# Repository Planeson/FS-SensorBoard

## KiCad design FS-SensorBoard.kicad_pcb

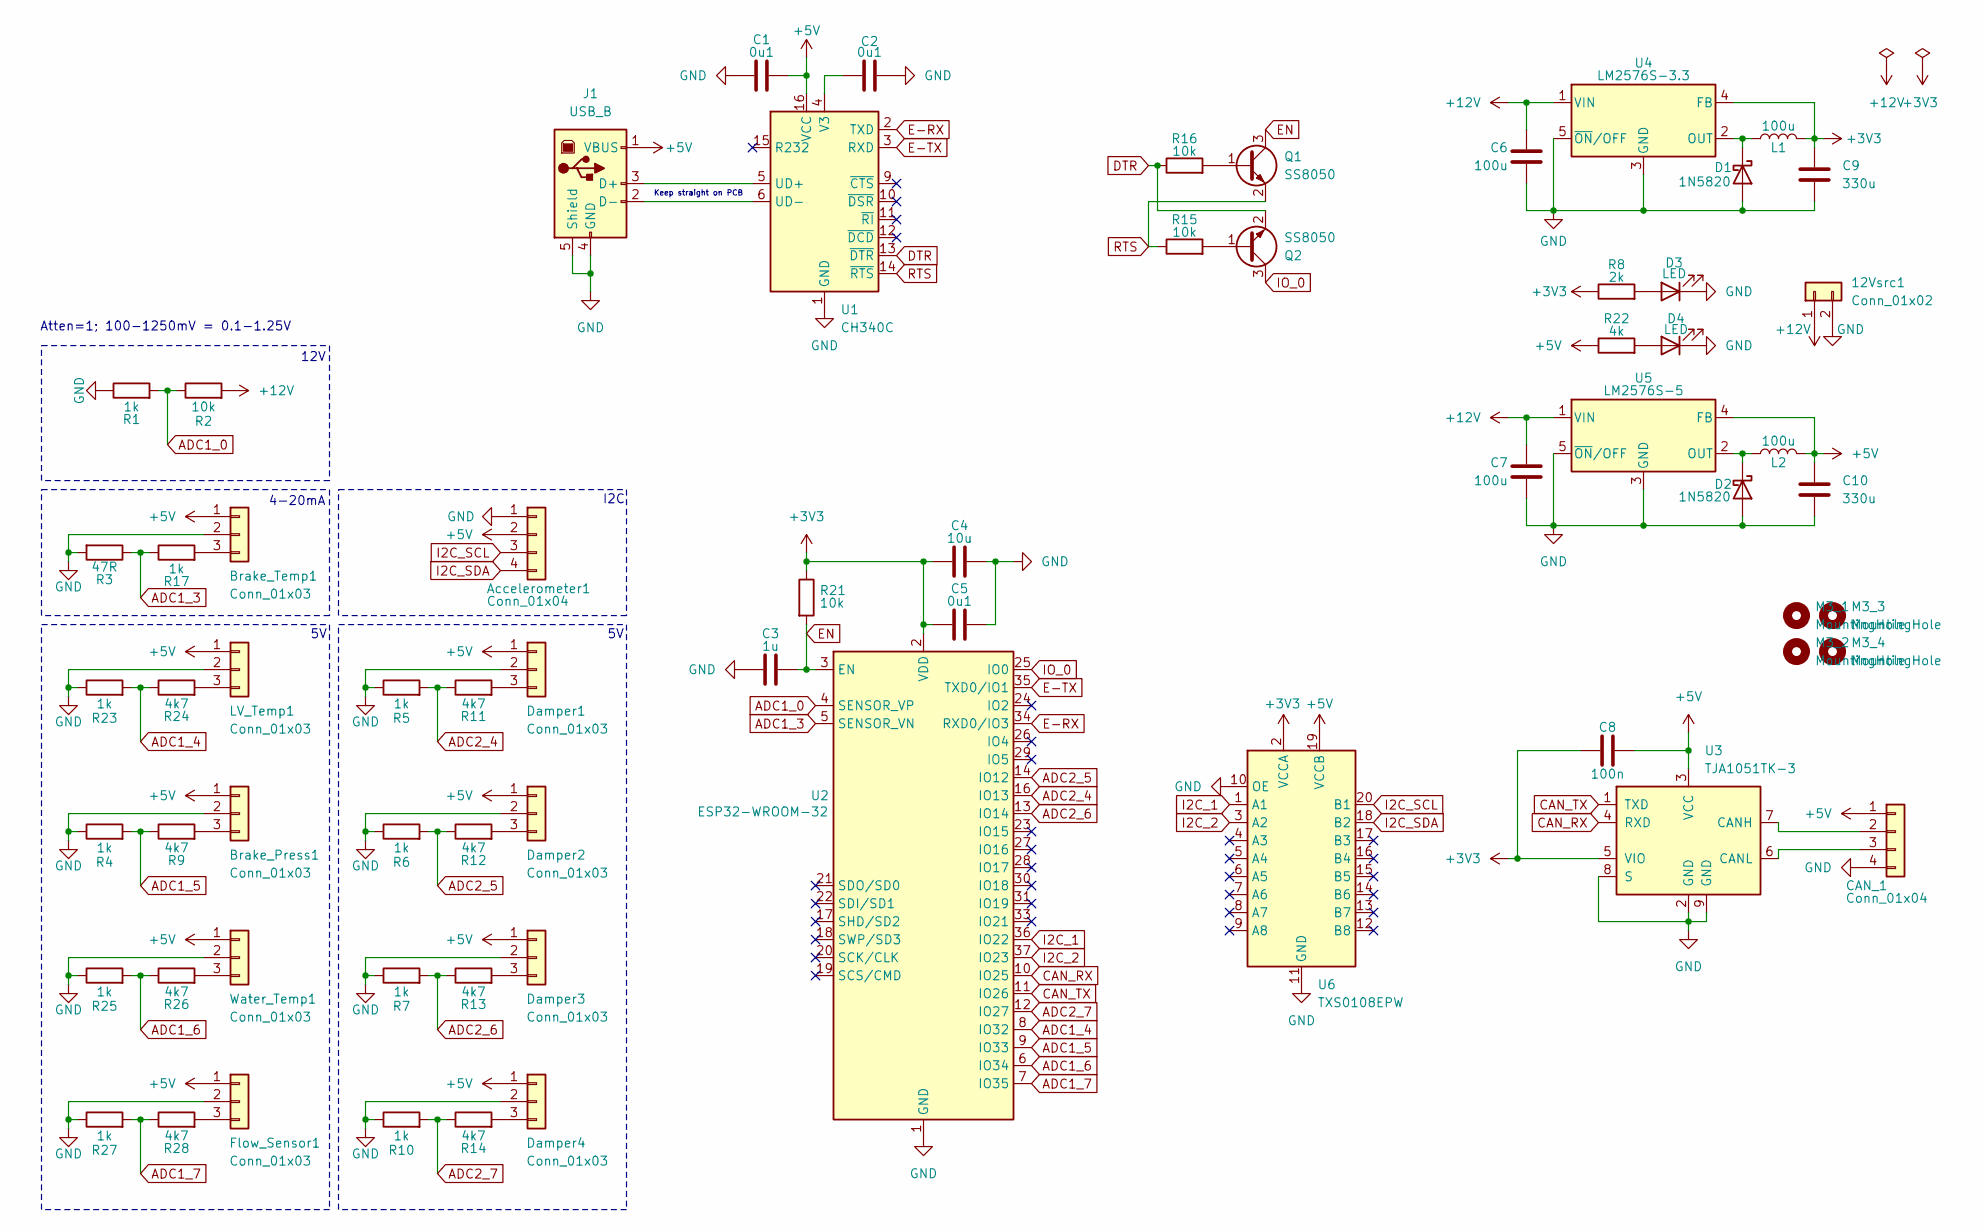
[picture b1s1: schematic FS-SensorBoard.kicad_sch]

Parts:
12Vsrc1: Conn_01x02; JST_VH_B2P-VH_1x02_P3.96mm_Vertical
Accelerometer1: Conn_01x04; JST_XH_B4B-XH-A_1x04_P2.50mm_Vertical
Brake_Press1: Conn_01x03; JST_XH_B3B-XH-A_1x03_P2.50mm_Vertical
Brake_Temp1: Conn_01x03; JST_XH_B3B-XH-A_1x03_P2.50mm_Vertical
C1, C2, C5: 0u1; C_1206_3216Metric_Pad1.33x1.80mm_HandSolder
C3: 1u; C_1206_3216Metric_Pad1.33x1.80mm_HandSolder
C4: 10u; C_1206_3216Metric_Pad1.33x1.80mm_HandSolder
C6, C7: 100u; C_1206_3216Metric_Pad1.33x1.80mm_HandSolder
C8: 100n; C_1206_3216Metric_Pad1.33x1.80mm_HandSolder
C9, C10: 330u; C_1808_4520Metric_Pad1.72x2.30mm_HandSolder
CAN_1: Conn_01x04; JST_XH_B4B-XH-A_1x04_P2.50mm_Vertical
D1, D2: 1N5820; D_DO-201AD_P15.24mm_Horizontal
D3, D4: LED; LED_1206_3216Metric_Pad1.42x1.75mm_HandSolder
Damper1, Damper2, Damper3, Damper4: Conn_01x03; JST_XH_B3B-XH-A_1x03_P2.50mm_Vertical
Flow_Sensor1: Conn_01x03; JST_XH_B3B-XH-A_1x03_P2.50mm_Vertical
J1: USB_B; USB_B_TE_5787834_Vertical
L1, L2: 100u; L_Bourns-SRN4018
LV_Temp1: Conn_01x03; JST_XH_B3B-XH-A_1x03_P2.50mm_Vertical
M3_1, M3_2, M3_3, M3_4: MountingHole; MountingHole_3.2mm_M3
Q1, Q2: SS8050; SOT-23
R1, R4, R5, R6, R7, R10, R17, R23, R25, R27: 1k; R_1206_3216Metric_Pad1.30x1.75mm_HandSolder
R2, R15, R16, R21: 10k; R_1206_3216Metric_Pad1.30x1.75mm_HandSolder
R3: 47R; R_1206_3216Metric_Pad1.30x1.75mm_HandSolder
R8: 2k; R_1206_3216Metric_Pad1.30x1.75mm_HandSolder
R9, R11, R12, R13, R14, R24, R26, R28: 4k7; R_1206_3216Metric_Pad1.30x1.75mm_HandSolder
R22: 4k; R_1206_3216Metric_Pad1.30x1.75mm_HandSolder
U1: CH340C; SOIC-16_3.9x9.9mm_P1.27mm
U2: ESP32-WROOM-32; ESP32-WROOM-32-LongPad
U3: TJA1051TK-3; DFN-8-1EP_3x3mm_P0.65mm_EP1.55x2.4mm
U4: LM2576S-3.3; TO-263-5_TabPin3
U5: LM2576S-5; TO-263-5_TabPin3
U6: TXS0108EPW; TSSOP-20_4.4x6.5mm_P0.65mm
Water_Temp1: Conn_01x03; JST_XH_B3B-XH-A_1x03_P2.50mm_Vertical

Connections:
+3V3: C4.1, C5.1, C8.1, C9.1, L1.2, R8.1, R21.1, U2.2 (VDD), U3.5 (VIO), U4.4 (FB), U6.2 (VCCA)
+5V: Accelerometer1.2, Brake_Press1.1, Brake_Temp1.1, C1.2, C8.2, C10.1, CAN_1.1, Damper1.1, Damper2.1, Damper3.1, Damper4.1, Flow_Sensor1.1, J1.1 (VBUS), L2.2, LV_Temp1.1, R22.1, U1.16 (VCC), U3.3 (VCC), U5.4 (FB), U6.19 (VCCB), Water_Temp1.1
+12V: 12Vsrc1.1, C6.1, C7.1, R2.2, U4.1 (VIN), U5.1 (VIN)
ADC1_0: R1.2, R2.1, U2.4 (SENSOR_VP)
ADC1_3: R3.1, R17.1, U2.5 (SENSOR_VN)
ADC1_4: R23.2, R24.1, U2.8 (IO32)
ADC1_5: R4.2, R9.1, U2.9 (IO33)
ADC1_6: R25.2, R26.1, U2.6 (IO34)
ADC1_7: R27.2, R28.1, U2.7 (IO35)
ADC2_4: R5.2, R11.1, U2.16 (IO13)
ADC2_5: R6.2, R12.1, U2.14 (IO12)
ADC2_6: R7.2, R13.1, U2.13 (IO14)
ADC2_7: R10.2, R14.1, U2.12 (IO27)
CAN_RX: U2.10 (IO25), U3.4 (RXD)
CAN_TX: U2.11 (IO26), U3.1 (TXD)
DTR: Q2.2 (E), R16.1, U1.13 (~DTR)
E-RX: U1.2 (TXD), U2.34 (RXD0/IO3)
E-TX: U1.3 (RXD), U2.35 (TXD0/IO1)
EN: C3.2, Q1.3 (C), R21.2, U2.3 (EN)
GND: 12Vsrc1.2, Accelerometer1.1, Brake_Press1.2, Brake_Temp1.2, C1.1, C2.1, C3.1, C4.2, C5.2, C6.2, C7.2, C9.2, C10.2, CAN_1.4, D1.2 (A), D2.2 (A), D3.1 (K), D4.1 (K), Damper1.2, Damper2.2, Damper3.2, Damper4.2, Flow_Sensor1.2, J1.4 (GND), J1.5 (Shield), LV_Temp1.2, R1.1, R3.2, R4.1, R5.1, R6.1, R7.1, R10.1, R23.1, R25.1, R27.1, U1.1 (GND), U2.1 (GND), U2.15 (GND), U2.38 (GND), U2.39 (GND), U3.2 (GND), U3.8 (S), U3.9 (GND), U4.3 (GND), U4.5 (~ON/OFF), U5.3 (GND), U5.5 (~ON/OFF), U6.10 (OE), U6.11 (GND), Water_Temp1.2
I2C_1: U2.36 (IO22), U6.1 (A1)
I2C_2: U2.37 (IO23), U6.3 (A2)
I2C_SCL: Accelerometer1.3, U6.20 (B1)
I2C_SDA: Accelerometer1.4, U6.18 (B2)
IO_0: Q2.3 (C), U2.25 (IO0)
unnamed: Brake_Press1.3, R9.2
unnamed: Brake_Temp1.3, R17.2
unnamed: CAN_1.2, U3.7 (CANH)
unnamed: CAN_1.3, U3.6 (CANL)
unnamed: D1.1 (K), L1.1, U4.2 (OUT)
unnamed: D2.1 (K), L2.1, U5.2 (OUT)
unnamed: D3.2 (A), R8.2
unnamed: D4.2 (A), R22.2
unnamed: Damper1.3, R11.2
unnamed: Damper2.3, R12.2
unnamed: Damper3.3, R13.2
unnamed: Damper4.3, R14.2
unnamed: Flow_Sensor1.3, R28.2
unnamed: J1.3 (D+), U1.5 (UD+)
unnamed: J1.2 (D-), U1.6 (UD-)
unnamed: LV_Temp1.3, R24.2
unnamed: Q1.1 (B), R16.2
unnamed: Q2.1 (B), R15.2
unnamed: C2.2, U1.4 (V3)
unnamed: R26.2, Water_Temp1.3
RTS: Q1.2 (E), R15.1, U1.14 (~RTS)

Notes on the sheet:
4-20mA
Keep straight on PCB
12V
Atten=1; 100-1250mV = 0.1-1.25V
I2C

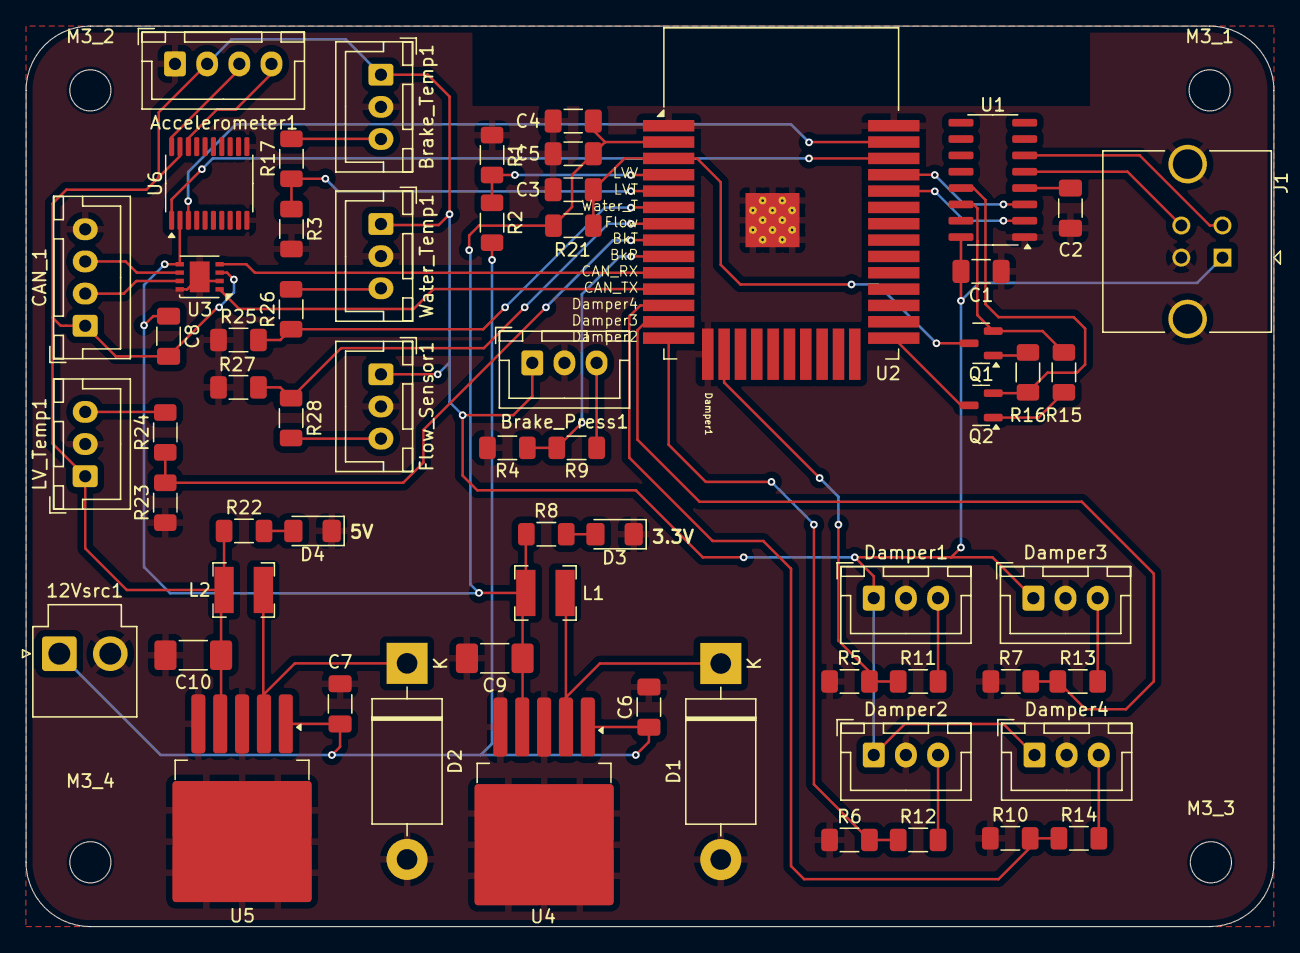
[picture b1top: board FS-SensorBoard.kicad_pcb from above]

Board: 2 copper layers, 97.0 x 70.0 mm, 66 parts (0 on the bottom side), 46 nets.

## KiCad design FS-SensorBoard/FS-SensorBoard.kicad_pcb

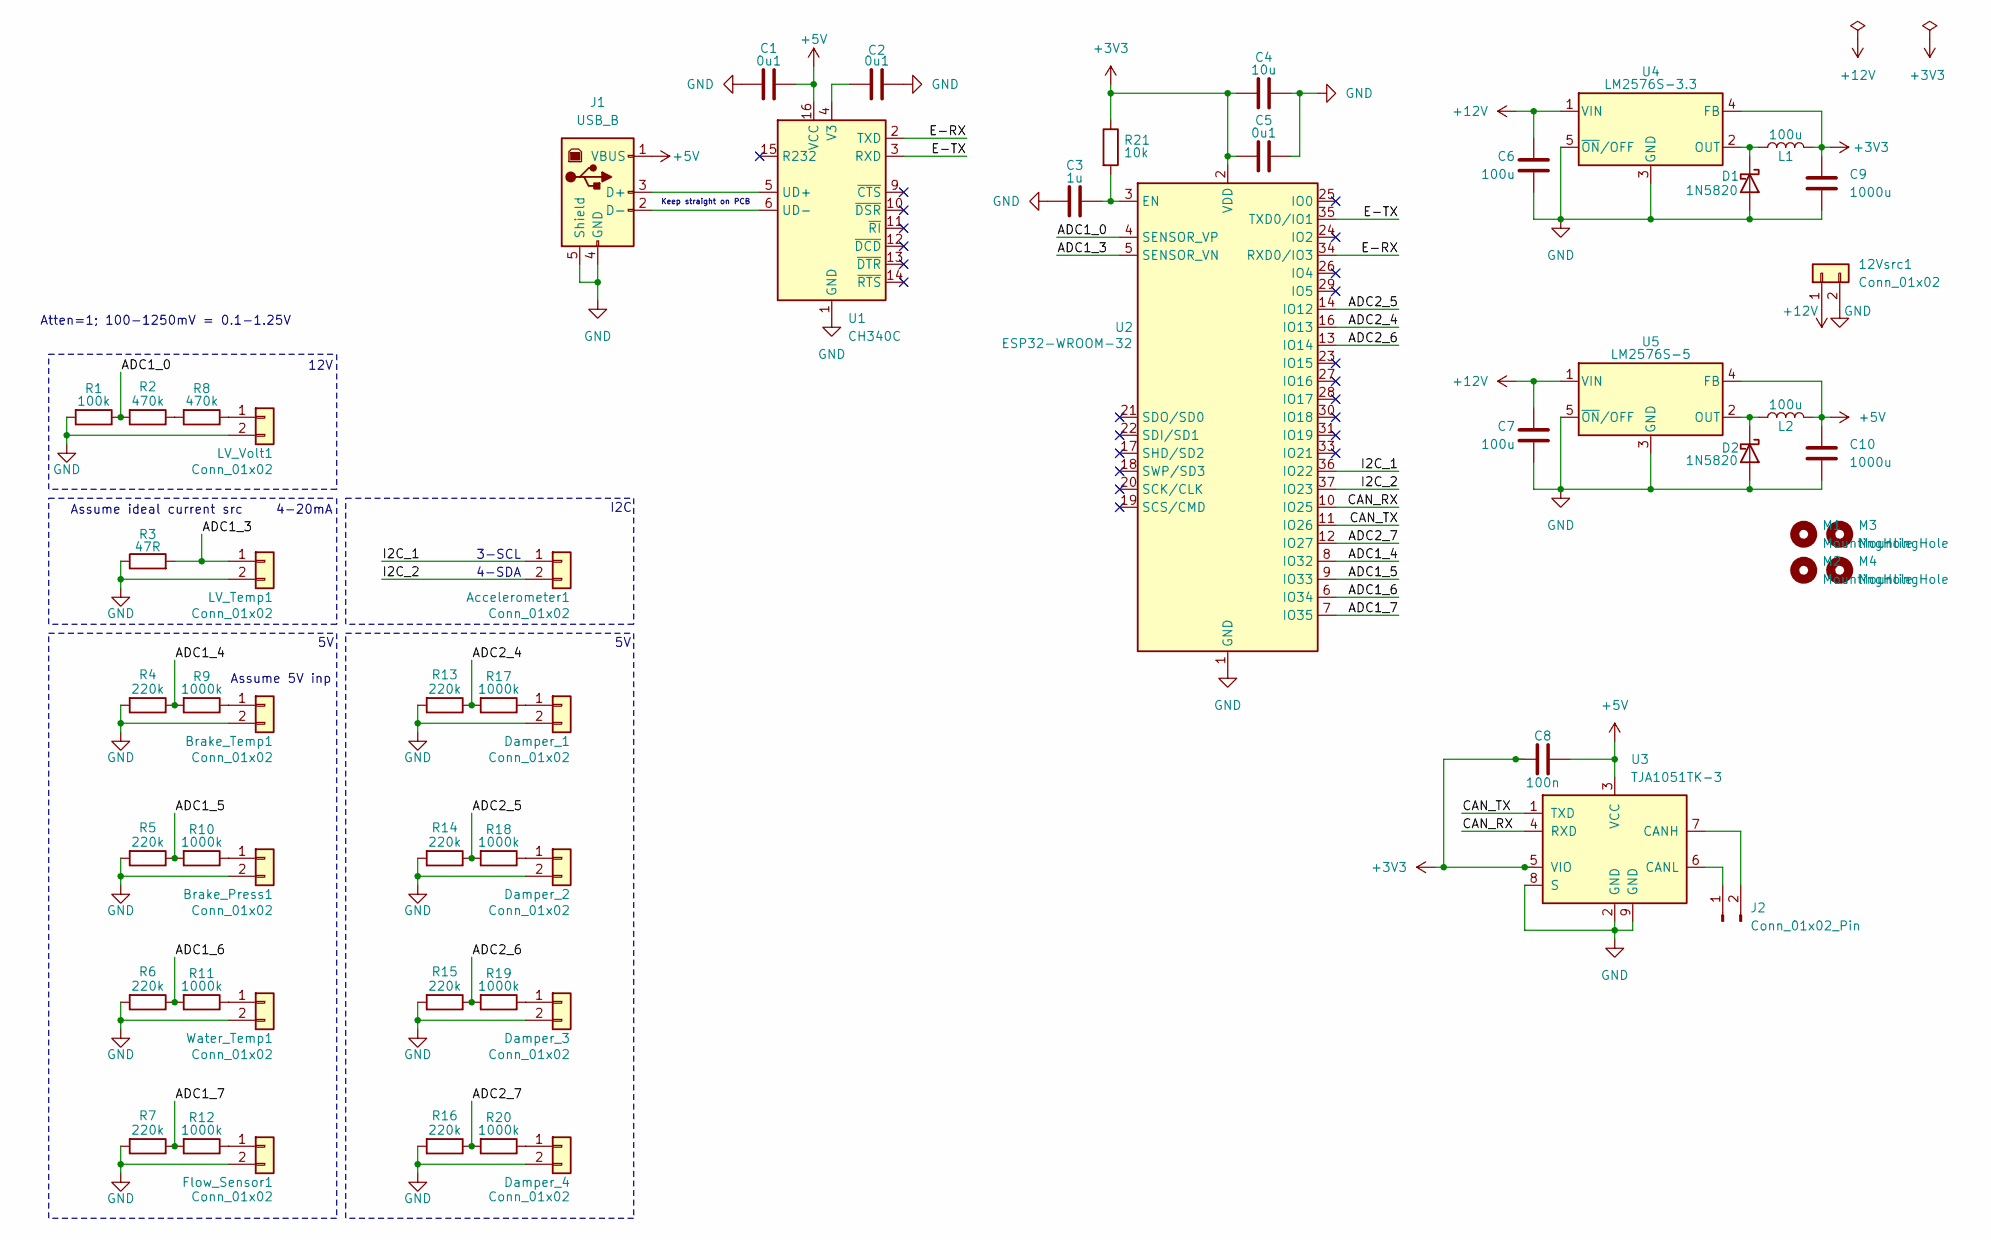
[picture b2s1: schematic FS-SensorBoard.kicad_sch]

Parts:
12Vsrc1: Conn_01x02; JST_VH_B2P-VH_1x02_P3.96mm_Vertical
Accelerometer1: Conn_01x02; JST_XH_B2B-XH-A_1x02_P2.50mm_Vertical
Brake_Press1: Conn_01x02; JST_XH_B2B-XH-A_1x02_P2.50mm_Vertical
Brake_Temp1: Conn_01x02; JST_XH_B2B-XH-A_1x02_P2.50mm_Vertical
C1, C2, C5: 0u1; C_1206_3216Metric_Pad1.33x1.80mm_HandSolder
C3: 1u; C_1206_3216Metric_Pad1.33x1.80mm_HandSolder
C4: 10u; C_1206_3216Metric_Pad1.33x1.80mm_HandSolder
C6, C7: 100u; C_1206_3216Metric_Pad1.33x1.80mm_HandSolder
C8: 100n; C_1206_3216Metric_Pad1.33x1.80mm_HandSolder
C9, C10: 1000u; C_1206_3216Metric_Pad1.33x1.80mm_HandSolder
D1, D2: 1N5820; D_DO-201AD_P15.24mm_Horizontal
Damper_1, Damper_2, Damper_3, Damper_4: Conn_01x02; JST_XH_B2B-XH-A_1x02_P2.50mm_Vertical
Flow_Sensor1: Conn_01x02; JST_XH_B2B-XH-A_1x02_P2.50mm_Vertical
J1: USB_B; USB_B_TE_5787834_Vertical
J2: Conn_01x02_Pin; JST_XH_B2B-XH-A_1x02_P2.50mm_Vertical
L1, L2: 100u; L_1206_3216Metric_Pad1.22x1.90mm_HandSolder
LV_Temp1: Conn_01x02; JST_XH_B2B-XH-A_1x02_P2.50mm_Vertical
LV_Volt1: Conn_01x02; JST_XH_B2B-XH-A_1x02_P2.50mm_Vertical
M1, M2, M3, M4: MountingHole; MountingHole_3.2mm_M3
R1: 100k; R_1206_3216Metric_Pad1.30x1.75mm_HandSolder
R2, R8: 470k; R_1206_3216Metric_Pad1.30x1.75mm_HandSolder
R3: 47R; R_1206_3216Metric_Pad1.30x1.75mm_HandSolder
R4, R5, R6, R7, R13, R14, R15, R16: 220k; R_1206_3216Metric_Pad1.30x1.75mm_HandSolder
R9, R10, R11, R12, R17, R18, R19, R20: 1000k; R_1206_3216Metric_Pad1.30x1.75mm_HandSolder
R21: 10k; R_1206_3216Metric_Pad1.30x1.75mm_HandSolder
U1: CH340C; SOIC-16_3.9x9.9mm_P1.27mm
U2: ESP32-WROOM-32
U3: TJA1051TK-3; DFN-8-1EP_3x3mm_P0.65mm_EP1.55x2.4mm
U4: LM2576S-3.3; TO-263-5_TabPin3
U5: LM2576S-5; TO-263-5_TabPin3
Water_Temp1: Conn_01x02; JST_XH_B2B-XH-A_1x02_P2.50mm_Vertical

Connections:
+3V3: C4.1, C5.1, C8.1, C9.1, L1.2, R21.1, U2.2 (VDD), U3.5 (VIO), U4.4 (FB)
+5V: C1.2, C8.2, C10.1, J1.1 (VBUS), L2.2, U1.16 (VCC), U3.3 (VCC), U5.4 (FB)
+12V: 12Vsrc1.1, C6.1, C7.1, U4.1 (VIN), U5.1 (VIN)
/ADC1_0: R1.1, R2.2, U2.4 (SENSOR_VP)
/ADC1_3: LV_Temp1.1, R3.2, U2.5 (SENSOR_VN)
/ADC1_4: R4.1, R9.2, U2.8 (IO32)
/ADC1_5: R5.1, R10.2, U2.9 (IO33)
/ADC1_6: R6.1, R11.2, U2.6 (IO34)
/ADC1_7: R7.1, R12.2, U2.7 (IO35)
/ADC2_4: R13.1, R17.2, U2.16 (IO13)
/ADC2_5: R14.1, R18.2, U2.14 (IO12)
/ADC2_6: R15.1, R19.2, U2.13 (IO14)
/ADC2_7: R16.1, R20.2, U2.12 (IO27)
/CAN_RX: U2.10 (IO25), U3.4 (RXD)
/CAN_TX: U2.11 (IO26), U3.1 (TXD)
/E-RX: U1.2 (TXD), U2.34 (RXD0/IO3)
/E-TX: U1.3 (RXD), U2.35 (TXD0/IO1)
/I2C_1: Accelerometer1.1, U2.36 (IO22)
/I2C_2: Accelerometer1.2, U2.37 (IO23)
GND: 12Vsrc1.2, Brake_Press1.2, Brake_Temp1.2, C1.1, C2.1, C3.1, C4.2, C5.2, C6.2, C7.2, C9.2, C10.2, D1.2 (A), D2.2 (A), Damper_1.2, Damper_2.2, Damper_3.2, Damper_4.2, Flow_Sensor1.2, J1.4 (GND), J1.5 (Shield), LV_Temp1.2, LV_Volt1.2, R1.2, R3.1, R4.2, R5.2, R6.2, R7.2, R13.2, R14.2, R15.2, R16.2, U1.1 (GND), U2.1 (GND), U2.15 (GND), U2.38 (GND), U2.39 (GND), U3.2 (GND), U3.8 (S), U3.9 (GND), U4.3 (GND), U4.5 (~ON/OFF), U5.3 (GND), U5.5 (~ON/OFF), Water_Temp1.2
unnamed: Brake_Press1.1, R10.1
unnamed: Brake_Temp1.1, R9.1
unnamed 22: J2.1, U3.6 (CANL); also elsewhere on the board
unnamed 23: J2.2, U3.7 (CANH); also elsewhere on the board
unnamed: D1.1 (K), L1.1, U4.2 (OUT)
unnamed: D2.1 (K), L2.1, U5.2 (OUT)
unnamed: Damper_1.1, R17.1
unnamed: Damper_2.1, R18.1
unnamed: Damper_3.1, R19.1
unnamed: Damper_4.1, R20.1
unnamed: Flow_Sensor1.1, R12.1
unnamed: J1.3 (D+), U1.5 (UD+)
unnamed: J1.2 (D-), U1.6 (UD-)
unnamed: LV_Volt1.1, R8.1
unnamed: R2.1, R8.2
unnamed: C2.2, U1.4 (V3)
unnamed: C3.2, R21.2, U2.3 (EN)
unnamed: R11.1, Water_Temp1.1

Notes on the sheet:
4-20mA
Keep straight on PCB
Assume ideal current src
Assume 5V inp
12V
3-SCL
4-SDA
Atten=1; 100-1250mV = 0.1-1.25V
I2C

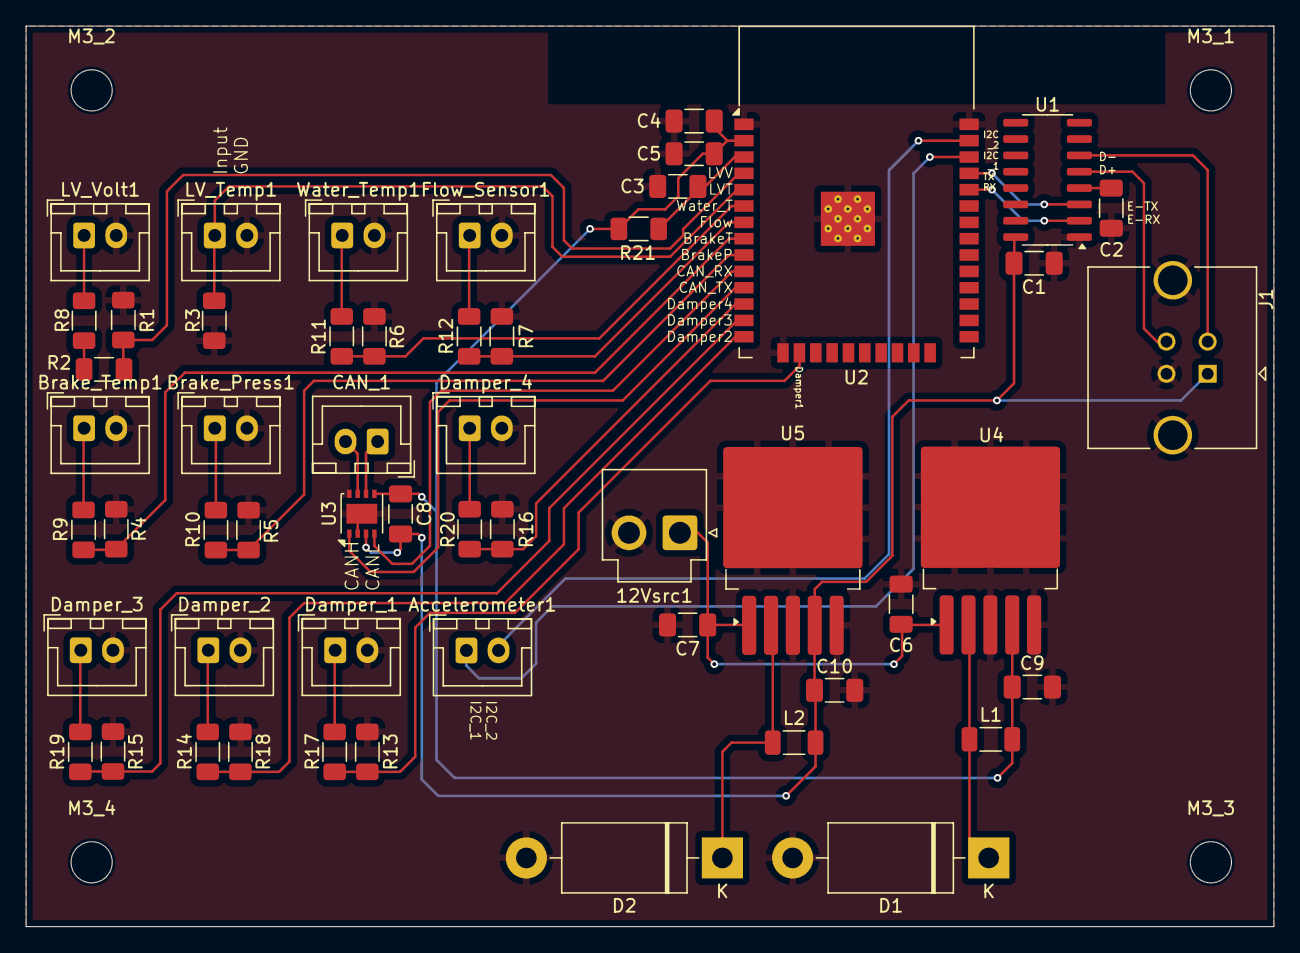
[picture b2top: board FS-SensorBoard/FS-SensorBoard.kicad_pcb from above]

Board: 2 copper layers, 97.0 x 70.0 mm, 58 parts (0 on the bottom side), 38 nets.

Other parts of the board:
CAN_1: Conn_01x02_Pin; JST_XH_B2B-XH-A_1x02_P2.50mm_Vertical
M3_1, M3_2, M3_3, M3_4: MountingHole; MountingHole_3.2mm_M3

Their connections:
unnamed 22: CAN_1.1; also elsewhere on the board
unnamed 23: CAN_1.2; also elsewhere on the board

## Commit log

2025-02-14 Pre-sleep version
2025-02-14 Tempfile Updates
2025-02-15 Version1
2025-02-15 Add silkscreens
2025-03-02 Start of V2
    Redesign - Minor progress towards V2:
    TODO:
    Correcting sensor pin
    Bootloader
    Larger pads
    Sensible size for caps, inductors, etc
2025-03-04 Completed Schematics
2025-03-04 Edited footprint
2025-03-05 V2.Garbage.0
